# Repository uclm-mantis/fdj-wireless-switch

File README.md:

# FdJ Wireless Switch

Primera versión del conmutador inalámbrico para juguetes adaptados. Utiliza ESP Now! sin cifrado y sin filtrado de fuente.

## Configuración del emisor

En `emisor/main/main.cpp` editar la definición de pulsadores. El campo `.id` se utiliza para ligarlo a la salida con el mismo valor en el receptor.

```c
pulsador pulsadores[] = {
    {  .pin = 44, .id = 1 },
    {  .pin = 7,  .id = 2 },
    {  .pin = 8,  .id = 3 },
    {  .pin = 9,  .id = 4 },
};
```

En el mismo archivo, justo a continuación, editar la definición de `peer`. Solo debería editarse la MAC en `.peer_addr` y el canal WiFi en `.channel`.

```c
esp_now_peer_info_t peer = {
    .peer_addr = { 0x40, 0x4C, 0xCA, 0xF9, 0xE6, 0x34 },
    .channel = 0,
    .encrypt = false
};
```

## Configuración del receptor

En `receptor/main/main.cpp` editar la definición de las salidas. El campo `.id` debe coincidir con el correspondiente emisor. El campo `.pinModoPulsador` es una entrada digital para configurar modo pulsador (*press* activa, *release* desactiva) o modo conmutador (*press* conmuta el estado).

```c
salida salidas[] = {
    { .id = 1, .pin = 6,   .pinModoPulsador = 0 },
    { .id = 2, .pin = 7,   .pinModoPulsador = 1 },
    { .id = 3, .pin = 8,   .pinModoPulsador = 3 },
    { .id = 4, .pin = 10,  .pinModoPulsador = 4 },
};
```

# TODO

- Mecanismo para configurar peer.
- Deep sleep al menos en emisor.

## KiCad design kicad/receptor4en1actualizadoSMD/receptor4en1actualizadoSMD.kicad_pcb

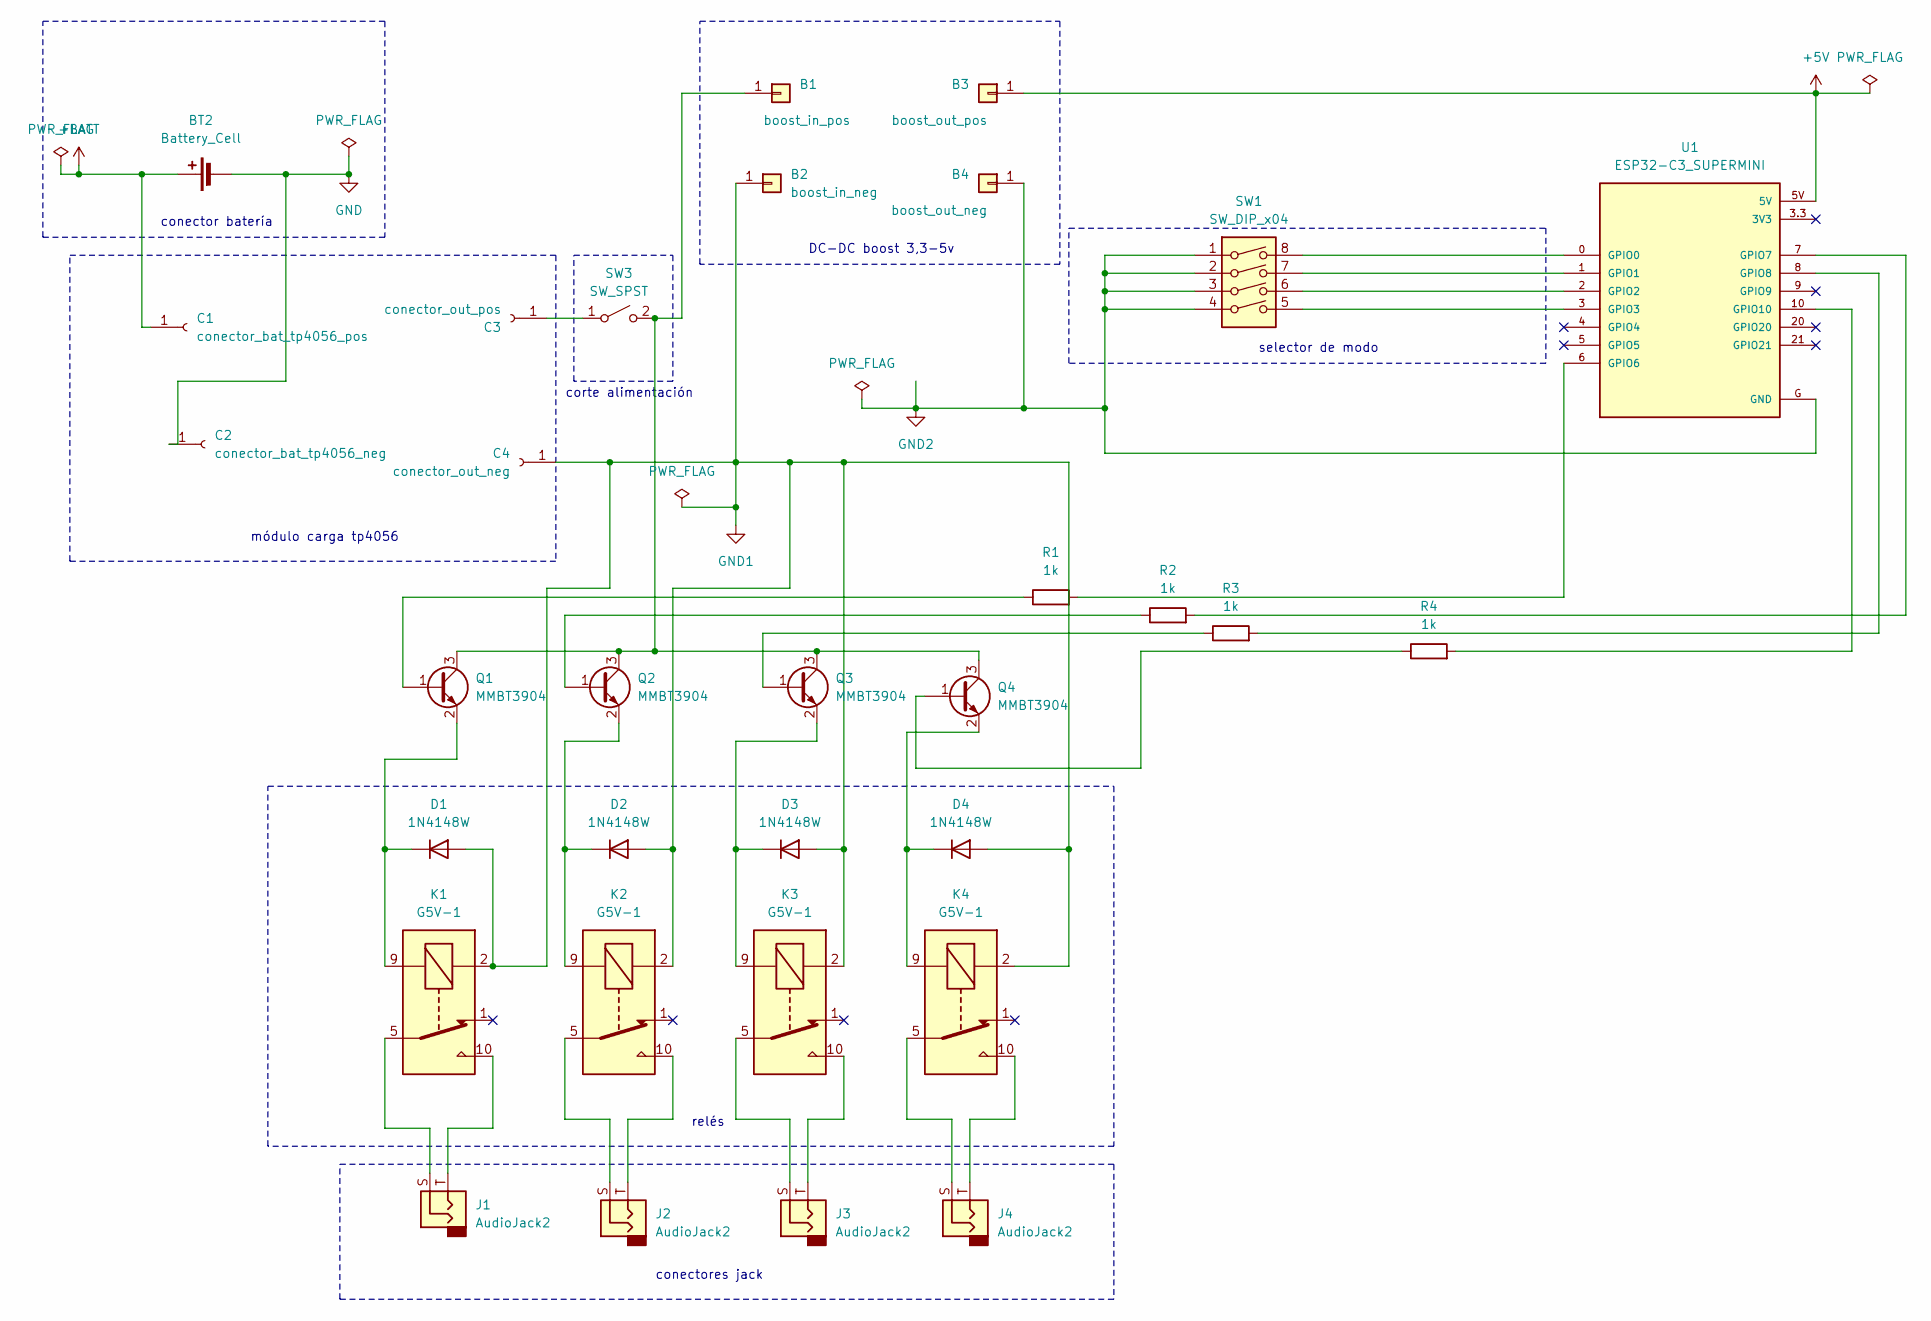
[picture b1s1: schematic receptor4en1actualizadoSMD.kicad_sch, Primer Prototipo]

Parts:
B1: boost_in_pos; PinHeader_1x01_P2.54mm_Vertical
B2: boost_in_neg; PinHeader_1x01_P2.54mm_Vertical
B3: boost_out_pos; PinHeader_1x01_P2.54mm_Vertical
B4: boost_out_neg; PinHeader_1x01_P2.54mm_Vertical
BT2: Battery_Cell; JST_PH_S2B-PH-K_1x02_P2.00mm_Horizontal
C1: conector_bat_tp4056_pos; PinHeader_1x01_P2.54mm_Vertical
C2: conector_bat_tp4056_neg; PinHeader_1x01_P2.54mm_Vertical
C3: conector_out_pos; PinHeader_1x01_P2.54mm_Vertical
C4: conector_out_neg; PinHeader_1x01_P2.54mm_Vertical
D1, D2, D3, D4: 1N4148W; D_SOD-123
J1, J2, J3, J4: AudioJack2; Jack_3.5mm_CUI_SJ1-3523N_Horizontal
K1, K2, K3, K4: G5V-1; Relay_SPDT_Omron_G5V-1
Q1, Q2, Q3, Q4: MMBT3904; SOT-23
R1, R2, R3, R4: 1k; R_0805_2012Metric_Pad1.20x1.40mm_HandSolder
SW1: SW_DIP_x04; DIP-8_W7.62mm_Socket
SW3: SW_SPST; JST_EH_S2B-EH_1x02_P2.50mm_Horizontal
U1: ESP32-C3_SUPERMINI; MODULE_ESP32-C3_SUPERMINI

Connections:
+5V: B3.1, U1.5V
+BATT: BT2.1 (+), C1.1
GND: BT2.2 (-), C2.1
GND1: B2.1, C4.1, D1.2 (A), D2.2 (A), D3.2 (A), D4.2 (A), K1.2, K2.2, K3.2, K4.2
GND2: B4.1, SW1.1, SW1.2, SW1.3, SW1.4, U1.G (GND)
unnamed: B1.1, Q1.3 (C), Q2.3 (C), Q3.3 (C), Q4.3 (C), SW3.2 (B)
unnamed: C3.1, SW3.1 (A)
unnamed: D1.1 (K), K1.9, Q1.2 (E)
unnamed: D2.1 (K), K2.9, Q2.2 (E)
unnamed: D3.1 (K), K3.9, Q3.2 (E)
unnamed: D4.1 (K), K4.9, Q4.2 (E)
unnamed: J1.S, K1.5, K1.6
unnamed: J1.T, K1.10
unnamed: J2.S, K2.5, K2.6
unnamed: J2.T, K2.10
unnamed: J3.S, K3.5, K3.6
unnamed: J3.T, K3.10
unnamed: J4.S, K4.5, K4.6
unnamed: J4.T, K4.10
unnamed: Q1.1 (B), R1.1
unnamed: Q2.1 (B), R2.1
unnamed: Q3.1 (B), R3.1
unnamed: Q4.1 (B), R4.1
unnamed: SW1.8, U1.0 (GPIO0)
unnamed: SW1.7, U1.1 (GPIO1)
unnamed: SW1.6, U1.2 (GPIO2)
unnamed: SW1.5, U1.3 (GPIO3)
unnamed: R1.2, U1.6 (GPIO6)
unnamed: R2.2, U1.7 (GPIO7)
unnamed: R3.2, U1.8 (GPIO8)
unnamed: R4.2, U1.10 (GPIO10)

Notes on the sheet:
conectores jack
selector de modo
relés
DC-DC boost 3,3-5v
corte alimentación
conector batería
módulo carga tp4056

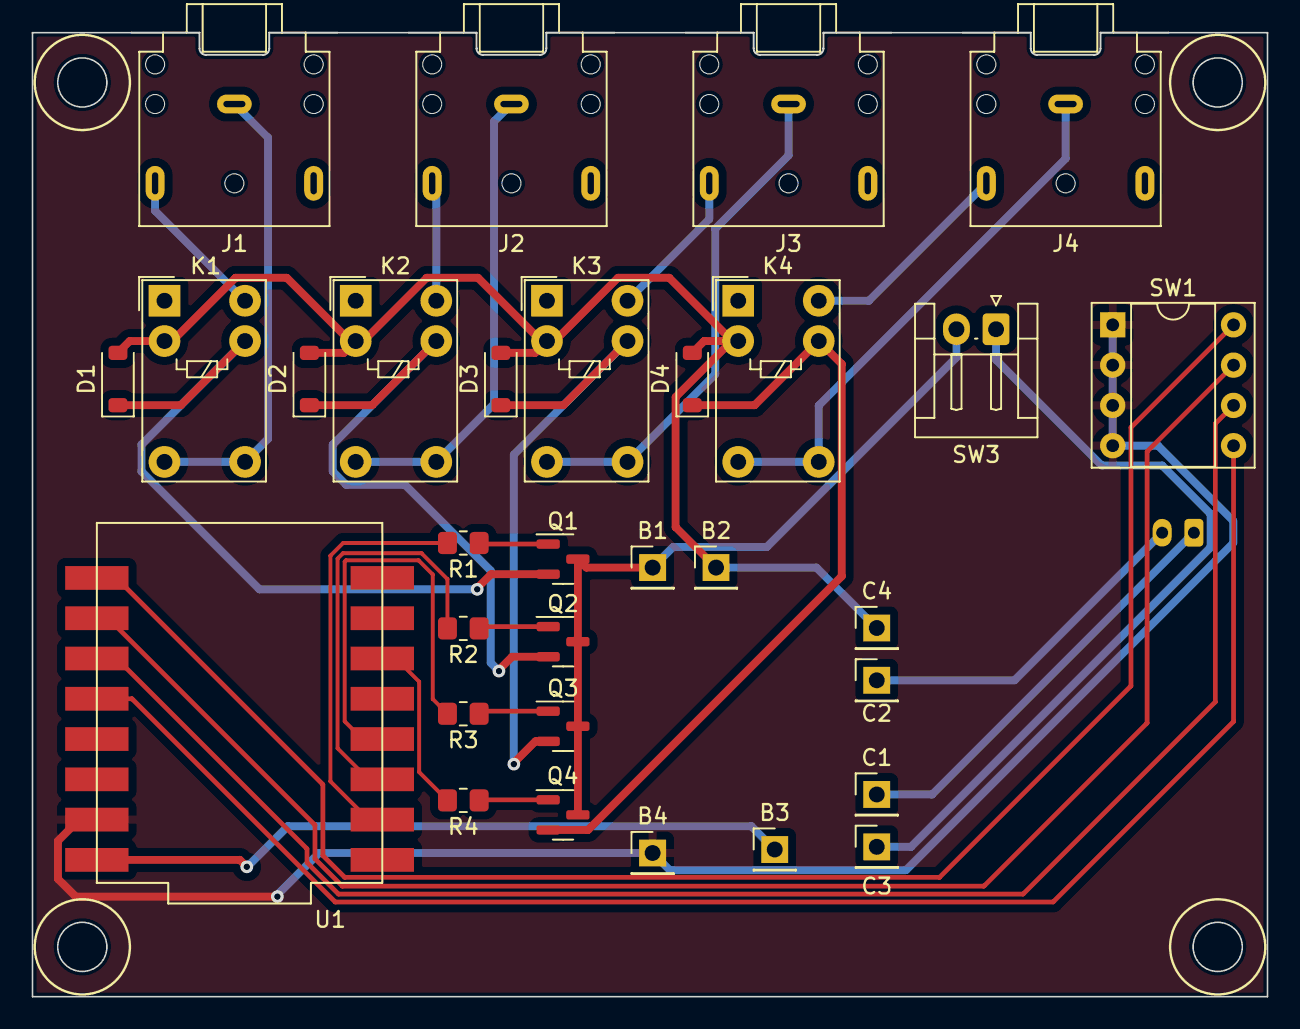
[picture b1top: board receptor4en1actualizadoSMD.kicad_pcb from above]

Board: 2 copper layers, 77.9 x 60.8 mm, 32 parts (1 on the bottom side), 31 nets.

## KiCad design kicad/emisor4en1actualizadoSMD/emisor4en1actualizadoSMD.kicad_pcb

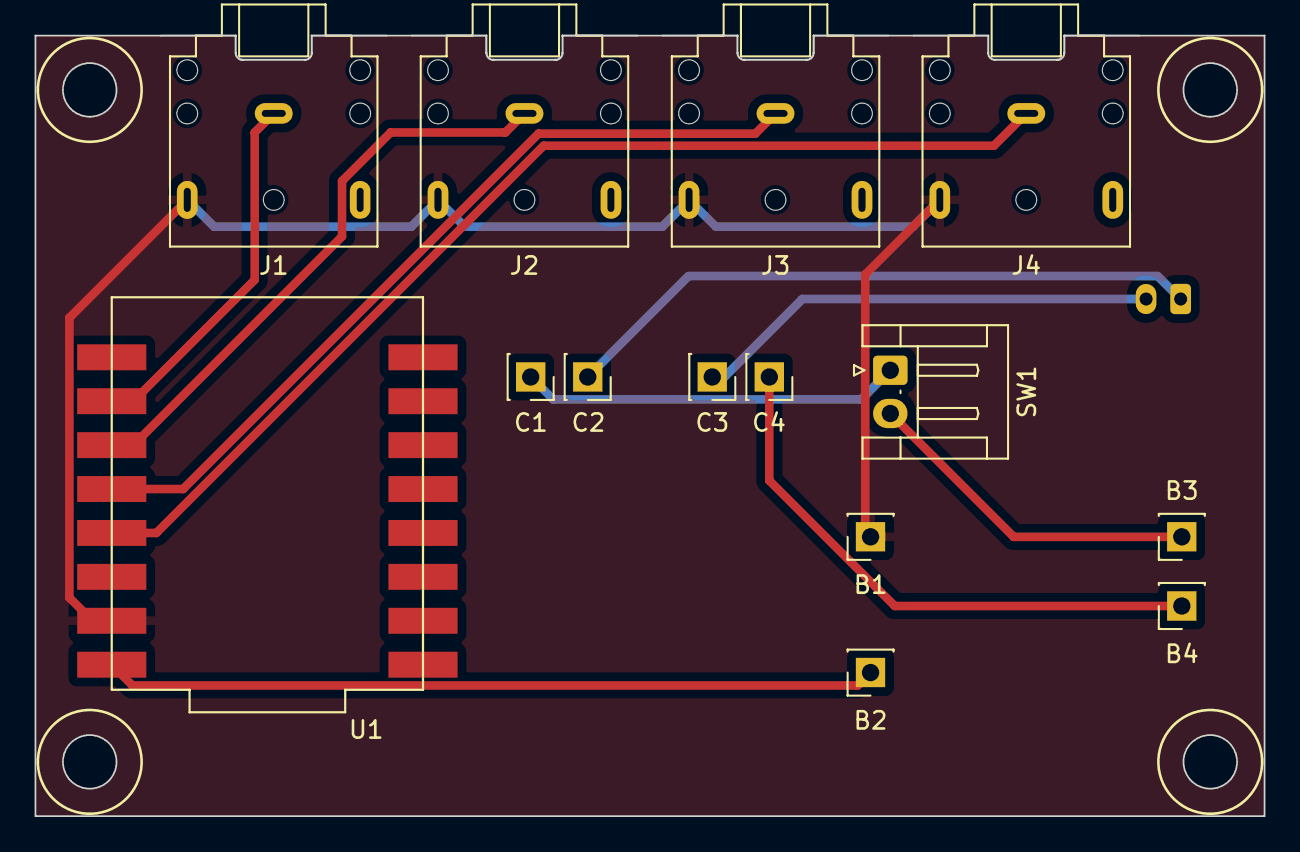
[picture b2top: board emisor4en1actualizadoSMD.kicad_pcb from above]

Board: 2 copper layers, 71.1 x 45.1 mm, 15 parts (1 on the bottom side), 11 nets.

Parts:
B1, B2, B3, B4: Conn_01x01; PinSocket_1x01_P2.54mm_Vertical
BT1: Battery_Cell; JST_PH_S2B-PH-K_1x02_P2.00mm_Horizontal
C1: con_out_pos; PinSocket_1x01_P2.54mm_Vertical
C2: con_bat_tp4056_pos; PinSocket_1x01_P2.54mm_Vertical
C3: con_bat_tp4056_neg; PinSocket_1x01_P2.54mm_Vertical
C4: con_bat_neg; PinSocket_1x01_P2.54mm_Vertical
J1, J2, J3, J4: AudioJack2; Jack_3.5mm_CUI_SJ1-3523N_Horizontal
SW1: SW_SPST; JST_EH_S2B-EH_1x02_P2.50mm_Horizontal
U1: ESP32-C3_SUPERMINI; MODULE_ESP32-C3_SUPERMINI

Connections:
+5V: B2.1, U1.5V
+BATT: BT1.1 (+), C2.1
GND: BT1.2 (-), C3.1
GND1: B4.1, C4.1
GND2: B1.1, J1.T, J2.T, J3.T, J4.T, U1.G (GND)
unnamed: C1.1, SW1.1 (A)
unnamed: B3.1, SW1.2 (B)
unnamed: J1.S, U1.1 (GPIO1)
unnamed: J2.S, U1.2 (GPIO2)
unnamed: J3.S, U1.3 (GPIO3)
unnamed: J4.S, U1.4 (GPIO4)

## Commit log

2024-03-07 First version wireless switch
    Caveats: no encryption, no channel selection, no peer selection.
2024-03-07 Configuración simplificada
2024-03-07 Untested version of non-arduino version
2024-03-07 Check if events lost
2024-03-07 Fixed emisor, still missing deep sleep
2024-03-07 fixed small bugs, tested in esp32c3
2024-03-07 Tested no-arduino branch, committing to master
2024-03-07 Squashed commit of the following:
    commit 17d71aa247266536494794c1b42f3f88f843305c
    Author: Francisco Moya <francisco.moya@uclm.es>
    Date: Thu Mar 7 20:20:40 2024 +0100
    Tested no-arduino branch, committing to master
    commit 7db730e6e573933042eab5c73b25572907f4b427
    Author: Francisco Moya <francisco.moya@uclm.es>
2024-03-09 Corregido comportamiento como conmutador
2024-04-19 actualización con test bench
2024-05-16 esquemas
